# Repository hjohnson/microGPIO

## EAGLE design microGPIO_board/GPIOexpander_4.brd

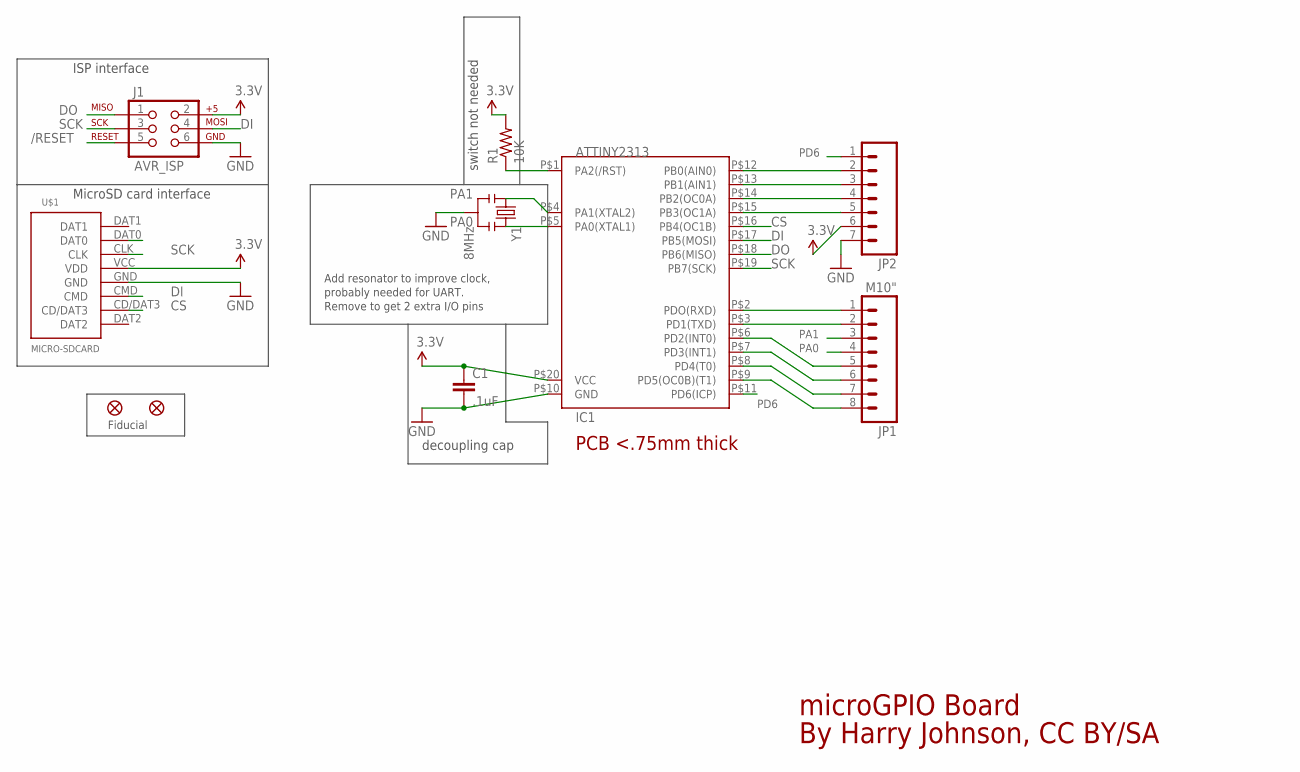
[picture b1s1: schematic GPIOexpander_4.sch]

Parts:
C1: .1uF; 0805
IC1: ATTINY2313; SO20W
J1: AVR_ISP; 2X3-NS
JP1: M10"; 1X08
JP2: M07; 1X07
R1: 10K; 0805
U$1: MICRO-SDCARD
U$2, U$3: FIDUCIAL1X2.5; FIDUCIAL-1X2.5
Y1: 8MHz; RESONATOR-SMD

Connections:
3.3V: C1.1, IC1.P$20 (VCC), J1.2, JP2.6, R1.2, U$1.VCC (VDD)
/RESET: IC1.P$1 (PA2(/RST)), J1.5, R1.1
CS: IC1.P$16 (PB4(OC1B)), U$1.CD/DAT3
DI: IC1.P$17 (PB5(MOSI)), J1.4, U$1.CMD
DO: IC1.P$18 (PB6(MISO)), J1.1, U$1.DAT0
GND: C1.2, IC1.P$10 (GND), J1.6, JP2.7, U$1.GND, Y1.2
PA0: IC1.P$5 (PA0(XTAL1)), JP1.4, Y1.3
PA1: IC1.P$4 (PA1(XTAL2)), JP1.3, Y1.1
PB0: IC1.P$12 (PB0(AIN0)), JP2.2
PB1: IC1.P$13 (PB1(AIN1)), JP2.3
PB2: IC1.P$14 (PB2(OC0A)), JP2.4
PB3: IC1.P$15 (PB3(OC1A)), JP2.5
PD0: IC1.P$2 (PDO(RXD)), JP1.1
PD1: IC1.P$3 (PD1(TXD)), JP1.2
PD2: IC1.P$6 (PD2(INT0)), JP1.5
PD3: IC1.P$7 (PD3(INT1)), JP1.6
PD4: IC1.P$8 (PD4(T0)), JP1.7
PD5: IC1.P$9 (PD5(OC0B)(T1)), JP1.8
PD6: IC1.P$11 (PD6(ICP)), JP2.1
SCK: IC1.P$19 (PB7(SCK)), J1.3, U$1.CLK

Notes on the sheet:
PCB <.75mm thick
MicroSD card interface
ISP interface
decoupling cap
switch not needed
Add resonator to improve clock,
Remove to get 2 extra I/O pins
probably needed for UART.
Fiducial
microGPIO Board
By Harry Johnson, CC BY/SA

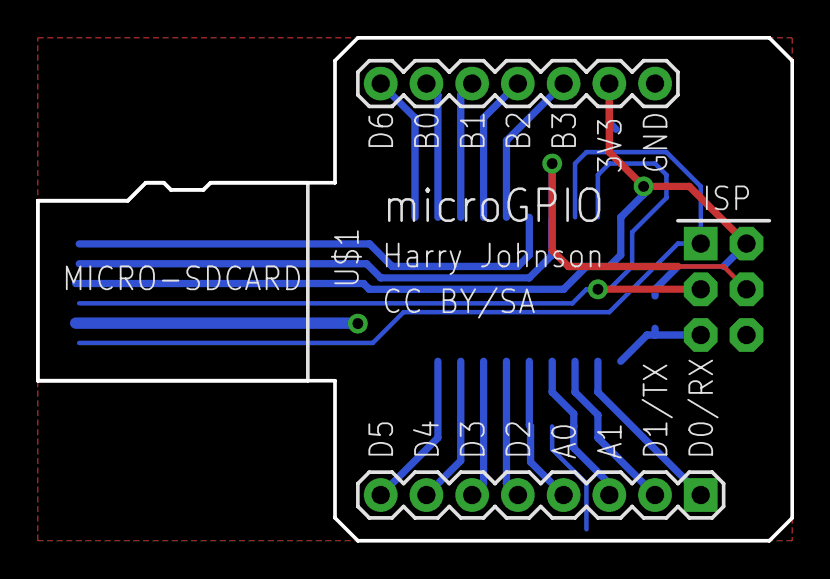
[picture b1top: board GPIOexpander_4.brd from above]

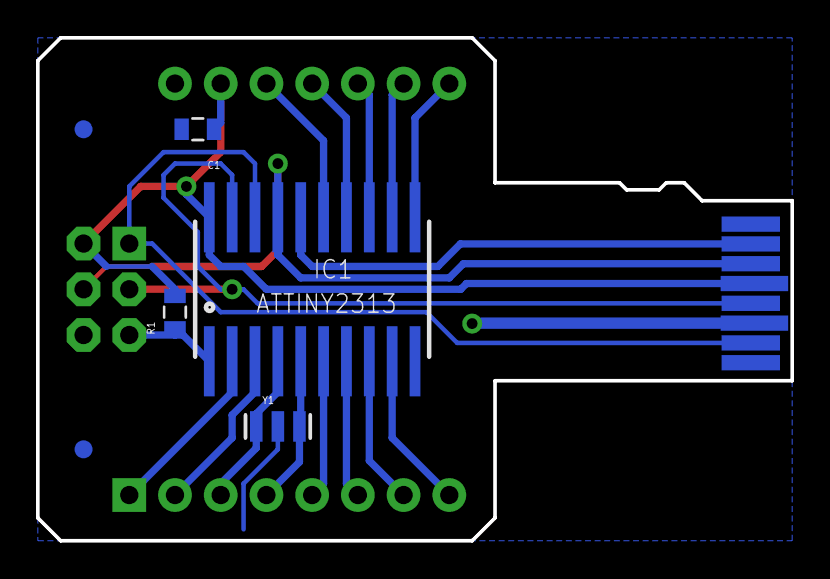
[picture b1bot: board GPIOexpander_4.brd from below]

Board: 2 copper layers, 41.9 x 27.9 mm, 10 parts (6 on the bottom side), 20 nets.

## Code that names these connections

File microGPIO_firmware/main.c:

/*
Filename: main.c for GPIO expander for the Adafruit/Rossum Microtouch.
Copyright (C) 2011  Harry Johnson

This program is free software; you can redistribute it and/or modify
it under the terms of the GNU Lesser Public License as published by
the Free Software Foundation; either version 2 of the License, or
(at your option) any later version.

This program is distributed in the hope that it will be useful,
but WITHOUT ANY WARRANTY; without even the implied warranty of
MERCHANTABILITY or FITNESS FOR A PARTICULAR PURPOSE.  See the
GNU Lesser Public License for more details.

You should have received a copy of the GNU Lesser Public License
along with this program; if not, write to the Free Software
Foundation, Inc., 59 Temple Place, Suite 330, Boston, MA  02111-1307  USA

Note: This was intended for use with the Microtouch, see www.adafruit.com, but was NOT designed or
reviewed by the original creators of the Microtouch.
*/

#include <avr/io.h> //ATTiny2313 Pin Definitions
#include <avr/interrupt.h> //interrupts.


#define USI_PORT PORTB
#define USI_PORT_IN PINB
#define USI_PORT_DIR DDRB
#define CS_PIN PB4
#define DI_PIN PB5
#define DO_PIN PB6
#define SCK_PIN PB7

//Pin Definitions
#define SPILED PB3
//End of pin definitions

volatile unsigned char heldUSIDR = 0; //the current data value.
unsigned char cmd[2] = {0}; //2 byte command/argument.

int expectByte = 0; //for command arguments.
int setConflict = 0; //is there a conflict on the SPI bus?
volatile int new =0; //Is the byte new?
volatile int SPI_enabled =0; //SPI enabled flag.

//SPI slave mode only.
void SPI_init(); //initialize SPI
void SPI_enable(); //enable SPI, reset counter, reset data register
void SPI_disable(); //disable SPI
unsigned char SPI_get(); //get the latest byte.
int SPI_isBusy(); //is the port in the process of shifting?
int SPI_put(unsigned char val); //queue up a byte.
int evalCommand(unsigned char command[2]);

int main(void)
{
	DDRD = 0xFF; //all output on port D.
	DDRB |= 0x0F; //outputs on the lower 4 bits.
	SPI_init(); //initialize the USI for slave SPI, set up pins.
    
	PORTD = 0; //turn off all inputs.
	
	for(;;){
		if(new==1) { //there is a new byte.
			if(expectByte == 0) { //this is the start of a new command.
				cmd[0] = SPI_get(); //store command.
				evalCommand(cmd); //evaluate the command, which here means say we anticipate a new byte.
			} else {
				cmd[1] = SPI_get(); //store argument.
				evalCommand(cmd); //evaluate command + argument.
				expectByte = 0; //back to waiting for a new command.
			}
		}
	} 
    return 0; //shouldn't reach here.
}

int evalCommand(unsigned char command[2]) {
	switch(command[0]) { //D, B turn on respective ports. More commands coming later.
		case 'D': if(expectByte==0) {expectByte=1;} else {PORTD = command[1]; } return 0; break; //if expectByte = 0, then this is the first byte of the command. 
		case 'B': if(expectByte==0) {expectByte=1;} else {PORTB = (command[1] & 0x07); } return 0; break;
		default: return 1; break; //error
	}	
}


/* SPI Code Begins Here */

void SPI_init() { //slave only
	PCMSK = (1<<PCINT4); //only the pin change 4 interrupt (Slave Select pin) is used.
	GIMSK |= (1<<PCIE); //enable the pin change interrupts in general.
	USI_PORT_DIR &= ~((1<<CS_PIN) | (1<<DI_PIN) | (1<<SCK_PIN) | (1<<DO_PIN)); // Everything input
	USI_PORT_DIR |= (1<<SPILED); //SPI enabled LED.
	USI_PORT &= ~((1<<DI_PIN) | (1<<SCK_PIN) | (1<<DO_PIN) | (1<<SPILED)); //remove pullups for all comm pins, turn off the indicator.
	USI_PORT |= (1<<CS_PIN); //enable pullup on CS pin
	USICR = (1<<USIWM0) | (1<<USICS1) | (0<<USICS0); //set wire mode and clock source (external via SCK pin)
	sei(); //enable interrupts.
}

void SPI_enable() {
	USISR &= 0xF0; //zero out the clock, so that inputs will be fresh again.
	USI_PORT_DIR |= (1<<DO_PIN); //DO pin needs to be set as output.
	USICR |= (1<<USIOIE); //enable the interrupt. 
	USIDR = 0; //zero out the data register.
	new = 0; //not a new byte at first.
	SPI_enabled = 1; //store that the SPI is enabled.
	USI_PORT |= (1<<SPILED); //turn on the SPI indicator LED. 
}

void SPI_disable() {
	USI_PORT_DIR &= ~(1<<DO_PIN); // inputs 
	USI_PORT &= ~((1<<DI_PIN) | (1<<SCK_PIN) | (1<<DO_PIN)); //remove pullups for all other pins.
	USICR &= ~(1<<USIOIE); //disable the counter interrupt.
	SPI_enabled = 0; //flag that SPI is off.
	USI_PORT &= ~(1<<SPILED); //turn off the SPI indicator LED.
}

int SPI_isBusy() {
	if((USISR & 0x0F) != 0 ) { // USI clock timer = 0 if USI is between bytes.
		setConflict = 1; //the port is still being updated, boo.
		return 1; //busy
	}
	setConflict = 0; //no conflict, yay!
	return 0; //not busy
}

int SPI_put(unsigned char val) { //Slave doesn't get to initiate send, but it can queue up data.
	if(SPI_isBusy() == 1) { //if there is still a byte being transferred, don't put our own data there.
		return -1; //Try again later!
	}
	USIDR = val; //if the line is quiet, queue up our own value to be sent out.
	return 0;
}

unsigned char SPI_get() { //gets the most recent value.
	return heldUSIDR;	
	new = 0; //the stored byte has already been read.
}

ISR(PCINT_vect) { //Slave select pin has changed, which only occurs at the beginning and the end of SPI usage.
	if((USI_PORT_IN & (1<<CS_PIN))==0) { //active low Slave Select pin.
		SPI_enable(); //if the pin is pulled low, then enable/reset the SPI.
	} else { 
		SPI_disable(); //if the pin is high, then disable the SPI.
	}

}

ISR(USI_OVERFLOW_vect) { //USI clock timer overflowed from 15 to 0, byte transfer complete.
	heldUSIDR = USIDR; //store the data
	new = 1; //there is a new byte.
	USISR |= (1<<USIOIF); //re-enable the USI timer interrupt.
}
/* SPI code ends here. */

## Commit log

2011-12-24 Added various files, schematics, boards, and firmware for the microGPIO and the micro touch.
2012-01-26 Fiddled with the board a bit.
